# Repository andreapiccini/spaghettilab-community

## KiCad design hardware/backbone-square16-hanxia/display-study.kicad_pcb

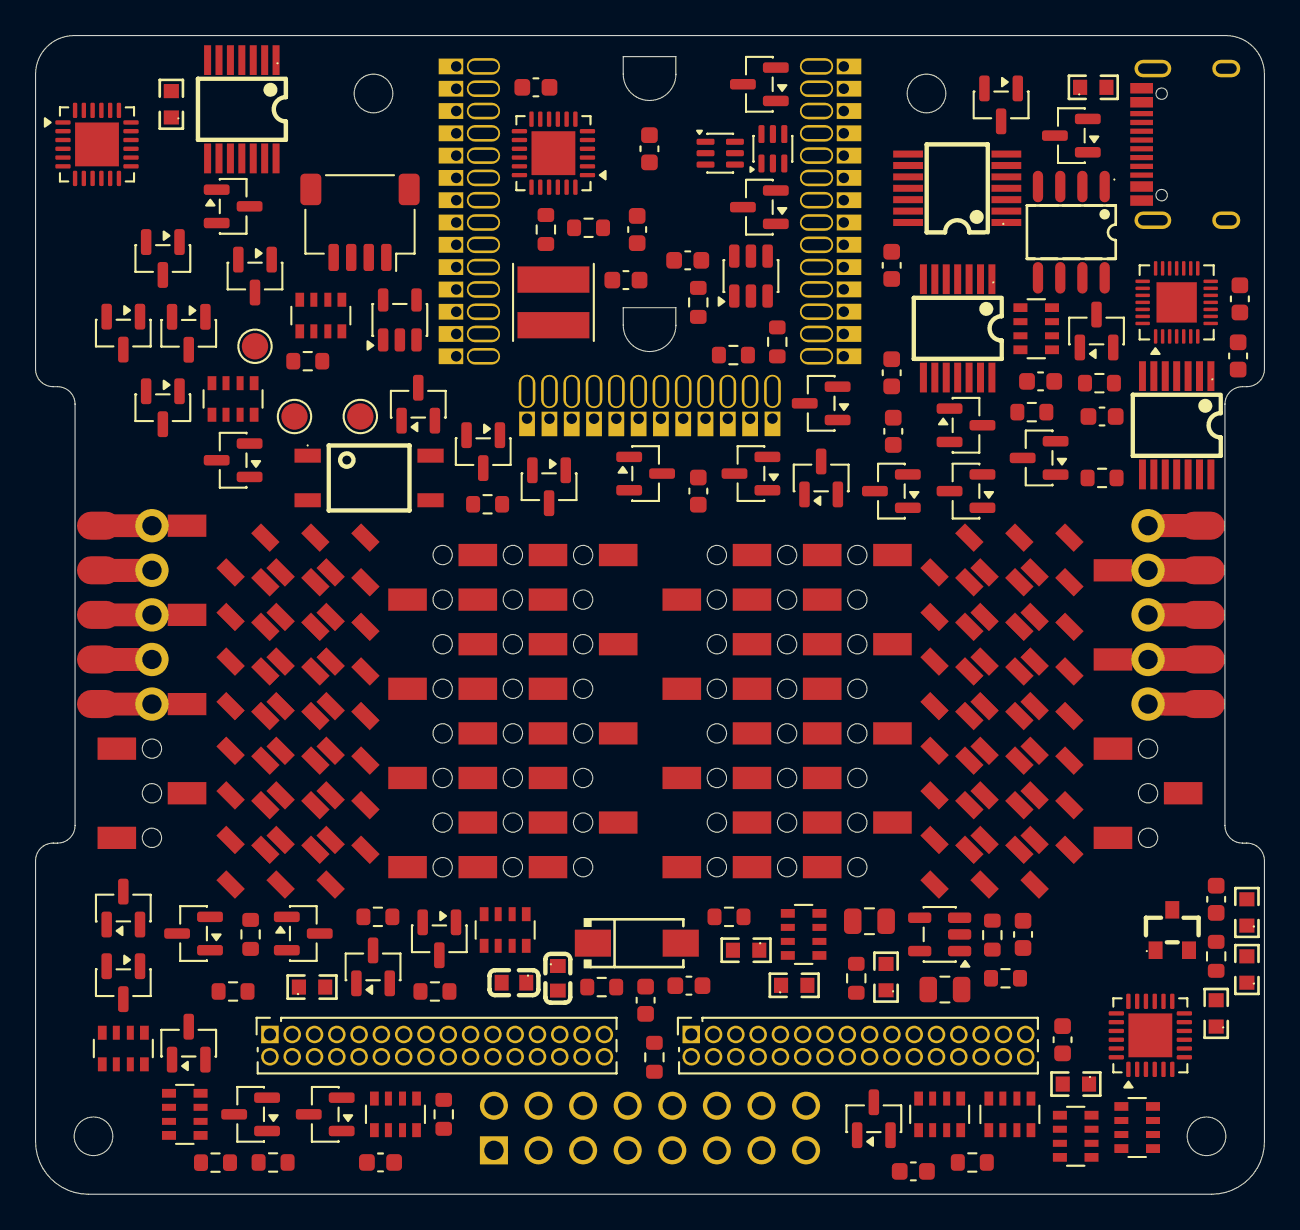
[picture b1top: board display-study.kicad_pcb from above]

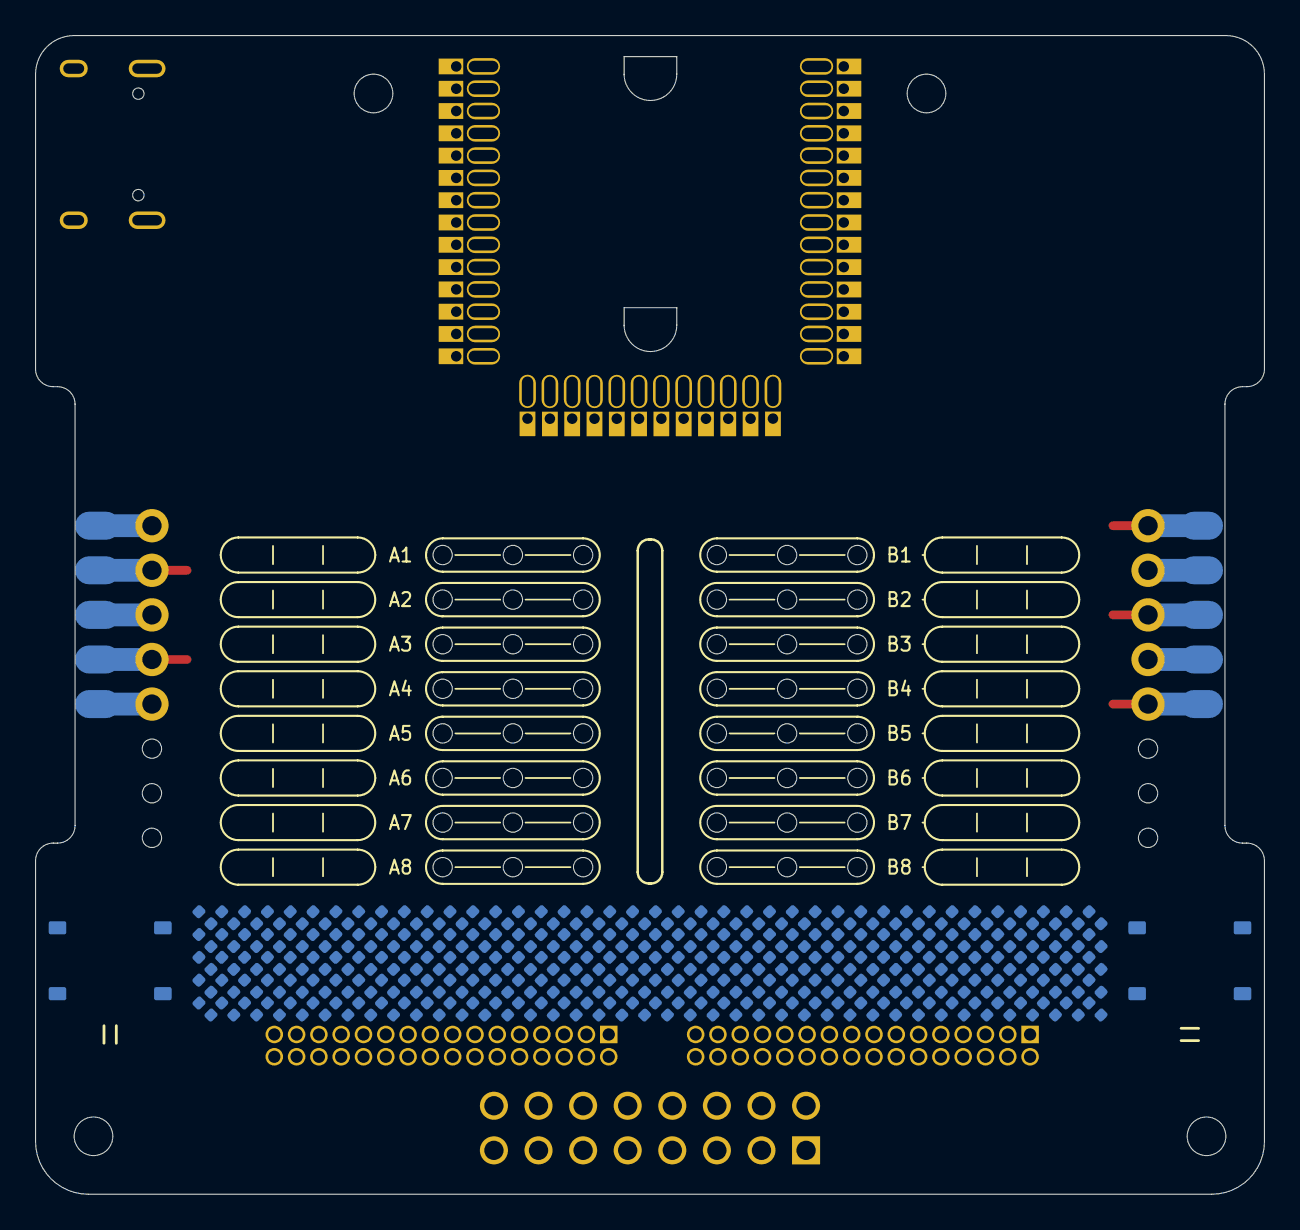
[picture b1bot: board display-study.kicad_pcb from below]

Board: 4 copper layers, 70.0 x 66.0 mm, 395 parts (203 on the bottom side), 150 nets.

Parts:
C1: 100nF/50V; C0603
C5, C9, C86: 22uF; C_0603_1608Metric
C11: 1uF; C0603
C74, C200, C204, C205, C206, C238, C239, C241, C242, C400, C402: 100nF; C_0603_1608Metric
C84: 22pF; C_0603_1608Metric
C85: 100nF/50V; C_0603_1608Metric
C139, C140: 10nF; C_0603_1608Metric
C299: 1nF; C_0603_1608Metric
C300, C301: 10uF 25V; C_0805_2012Metric
C401: 1uF; C_0603_1608Metric
D6: SS54_C22452; SMA_L4.4-W2.8-LS5.4-R-RD
D7: BAV70; SOT-23
D400, D403, D406, D409, D412, D415, D418, D421, D424, D427, D430, D433, D436, D439, D442, D445: XL-3216SURC-FB; XINGLIGHT_XL3216_Reverse_Word_Window
D401, D404, D407, D410, D413, D416, D419, D422, D425, D428, D431, D434, D437, D440, D443, D446: XL-3216UBC-FB; XINGLIGHT_XL3216_Reverse_Word_Window
D402, D405, D408, D411, D414, D417, D420, D423, D426, D429, D432, D435, D438, D441, D444, D447: XL-3216UGC-FB; XINGLIGHT_XL3216_Reverse_Word_Window
D500, D501, D502, D503, D504, D505, D506, D507, D508, D509, D510, D511, D512, D513, D514, D515, D516, D517, D518, D519, D520, D521, D522, D523, D524, D525, D526, D527, D528, D529, D530, D531, D532, D533, D534, D535, D536, D537, D538, D539, D540, D541, D542, D543, D544, D545, D546, D547, D548, D549, D550, D551, D552, D553, D554, D555, D556, D557, D558, D559, D560, D561, D562, D563, D564, D565, D566, D567, D568, D569, D570, D571, D572, D573, D574, D575, D576, D577, D578, D579, D580, D581, D582, D583, D584, D585, D586, D587, D588, D589, D590, D591, D592, D593, D594, D595, D596, D597, D598, D599, D600, D601, D602, D603, D604, D605, D606, D607, D608, D609, D610, D611, D612, D613, D614, D615, D616, D617, D618, D619, D620, D621, D622, D623, D624, D625, D626, D627, D628, D629, D630, D631, D632, D633, D634, D635, D636, D637, D638, D639, D640, D641, D642, D643, D644, D645, D646, D647, D648, D649, D650, D651, D652, D653, D654, D655, D656, D657, D658, D659, D660, D661, D662, D663, D664, D665, D666, D667, D668, D669, D670, D671, D672, D673, D674, D675, D676, D677, D678, D679, D680, D681, D682, D683, D684, D685, D686, D687, D688, D689, D690, D691, D692, D693, D694, D695, D696, D697, D698, D699: XL-1005SURC STUDY ONLY; LED_0402_1005Metric
H1, H2, H3, H4: MountingHole; MountingHole_2.2mm_M2_DIN965
J2: FROM_PREVIOUS; Magnetic_J2_PTH_Module
J4: SM04B-SRSS-TB(LF)(SN); JST_SH_SM04B-SRSS-TB_1x04-1MP_P1.00mm_Horizontal
J9: TO NEXT; Magnetic_J9_PTH_Module
J18, J19, J21, J22, J23, J24: HX PM2.54-1x8P TP-YQ; Hanxia_C42380985_1x08_BottomAccess_ContouredCourtyard
J25: BOOMELE 2x8 RA C52105; BOOMELE_C52105_2x08_RightAngle
J26, J27: MEZZ_2x16_P1.27; PinSocket_2x16_P1.27mm_Vertical
J28, J29: HX PM2.54-1x8P TP-YQ; Hanxia_C42380985_1x08_MagneticSharedHoles
L1: 3.3uH; L_XRTC404012S
Q2: AO3401A; SOT-23_L2.9-W1.3-P1.90-LS2.4-BR
Q9: LMBT3946DW1T1G; SOT-363_SC-70-6
Q10: LMBT3904DW1T1G; SOT-363_SC-70-6
Q30, Q31, Q32, Q33, Q34, Q35, Q36, Q37, Q44, Q45, Q46, Q47, Q48, Q49, Q50, Q51: AO3401A; SOT-23
Q100, Q101, Q102, Q103, Q104, Q105, Q106, Q107, Q108, Q109, Q110, Q111, Q112, Q113, Q114, Q115: AO3400A; SOT-23
R4, R123, R125, R126, R130, R203: 10k; R_0603_1608Metric
R5: 470R; R0603
R8: 120R; R0603
R15, R16: 10k; R0603
R17, R18: 33R; R0603
R22, R27: 5.1k; R0603
R24, R25: 4.7k; R0603
R36: 150k; R_0603_1608Metric
R37: 33.2k; R_0603_1608Metric
R104, R400: 47k; R_0603_1608Metric
R110: 56k; R_0603_1608Metric
R111, R124, R127, R129, R132, R200, R201, R202, R301: 100k; R_0603_1608Metric
R128, R131: 22k; R_0603_1608Metric
R300: 6.8k 1%; R_0603_1608Metric
R302, R303: 4.7k; R_0603_1608Metric
RN1, RN2, RN3, RN4, RN5, RN6, RN7, RN8, RN9, RN10, RN11, RN12: 100k; YC164_4x0603_100k
SW1, SW2: TS-1187A-B-A-B; XKB_TS1187A_5.1x5.1_H1.5
TP1: ESP_BOOT; TestPoint_Pad_D1.5mm
TP2: ESP_EN; TestPoint_Pad_D1.5mm
TP3: GND; TestPoint_Pad_D1.5mm
U1: ESP32-S3-WROOM-1-N8R2; ESP32-S3-WROOM-1_FlexyPin_N8R2_TwoSideCourtyard
U2: SN65HVD230DR; SOIC-8_L4.9-W3.9-P1.27-LS6.0-BL
U3: HC-TYPE-C-16P-01A; USB-C-SMD_HC-TYPE-C-16P-01A_ClearSilk
U4: SY8089AAAC; SOT-23-5
U8: G3VM-61VY3; SMD-4_L4.6-W3.7-P2.54-LS7.0-TL
U40, U41, U42: FCA9539Q; FCA9539Q_WQFN24_4x4
U50, U51, U53, U54: 74CBTLV3125PW,118; TSSOP-14_L5.0-W4.4-P0.65-LS6.4-BL
U60: SN74LVC1G97DBVR; SOT-23-6
U63: SY6280AAAC; SOT-23-5
U70: IS31FL3731-QFLS2-TR; IS31FL3731_QFN28_4x4

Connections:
3V3: C1.1, C9.1, C74.2, C84.1, C86.1, C200.1, C204.1, C205.1, C206.1, C238.1, C239.1, C241.1, C242.1, C300.1, J4.2 (+3V3), J25.3, J26.30, J27.28, J28.6, J29.6, L1.2, R15.1, R16.1, R24.1, R25.1, R36.1, R104.1, R302.1, R303.1, RN9.1, RN9.2, RN9.3, RN9.4, RN10.1, RN10.2, RN10.3, RN10.4, RN11.1, RN11.2, RN11.3, RN11.4, RN12.1, RN12.2, RN12.3, RN12.4, U1.2 (3V3), U2.3, U40.18, U40.21, U41.21, U41.23, U42.18, U42.21, U42.23, U50.14, U51.14, U53.14, U54.14, U60.5, U63.5
3V3_ROWS: C301.1, Q30.2, Q31.2, Q32.2, Q33.2, Q34.2, Q35.2, Q36.2, Q37.2, Q44.2, Q45.2, Q46.2, Q47.2, Q48.2, Q49.2, Q50.2, Q51.2, RN1.1, RN1.2, RN1.3, RN1.4, RN2.1, RN2.2, RN2.3, RN2.4, RN3.1, RN3.2, RN3.3, RN3.4, RN4.1, RN4.2, RN4.3, RN4.4, U63.1
5V: C5.1, C85.1, C140.1, C400.1, C401.1, D6.2, J2.1, J9.1, J25.4, J27.30, J28.5, J29.5, Q2.2, Q9.4, R4.1, R125.1, R127.1, R130.1, U4.1, U4.4, U70.2
BUCK_FB: C84.2, R36.2, R37.1, U4.5
BUCK_SW: L1.1, U4.3
CAN_H: J2.2, J9.2, J28.4, J29.4, R8.1, U2.7
CAN_L: J2.3, J9.3, J28.3, J29.3, U2.6, U8.4
CAN_RX: U1.11 (IO18), U2.4
CAN_TX: R104.2, U1.10 (IO17), U2.1
ESP_BOOT: R15.2, TP1.1, U1.27 (IO0), U60.6
ESP_EN: C11.2, J26.32, R16.2, TP2.1, U1.3 (EN), U60.1, U70.3
EXP_RESET_N: J27.32, R203.1, R301.1, U40.24, U41.24, U42.24, U60.4, U63.4
GND: C1.2, C5.2, C9.2, C11.1, C74.1, C85.2, C86.2, C139.2, C200.2, C204.2, C205.2, C206.2, C238.2, C239.2, C241.2, C242.2, C299.2, C300.2, C301.2, C400.2, C401.2, C402.2, J2.5, J4.1 (GND), J9.5, J25.1, J25.2, J25.14, J26.17, J26.19, J26.21, J26.23, J26.25, J26.27, J26.29, J26.31, J27.17, J27.19, J27.21, J27.23, J27.25, J27.27, J27.29, J27.31, J28.1, J29.1, Q9.1, Q10.1, Q10.4, Q100.2, Q101.2, Q102.2, Q103.2, Q104.2, Q105.2, Q106.2, Q107.2, Q108.2, Q109.2, Q110.2, Q111.2, Q112.2, Q113.2, Q114.2, Q115.2, R22.2, R27.1, R37.2, R111.2, R124.2, R129.2, R132.2, R200.2, R201.2, R202.2, R203.2, R300.2, R301.2, R400.2, RN5.5, RN5.6, RN5.7, RN5.8, RN6.5, RN6.6, RN6.7, RN6.8, RN7.5, RN7.6, RN7.7, RN7.8, RN8.5, RN8.6, RN8.7, RN8.8, SW1.2, SW2.2, TP3.1, U1.1 (GND), U1.40 (GND), U2.2, U2.8, U3.1 (SHELL), U3.2 (SHELL), U3.3 (SHELL), U3.4 (SHELL), U3.A1B12 (GND), U3.B1A12 (GND), U4.2, U8.2, U40.9, U40.23, U40.25, U41.9, U41.18, U41.25, U42.9, U42.25, U50.7, U51.7, U53.7, U54.7, U60.2, U60.3, U63.2, U70.5, U70.17, U70.18, U70.29
GPIO1: J26.2, U1.39 (IO1), U50.2
GPIO2: J26.4, U1.38 (IO2), U50.5
GPIO3: J26.6, R200.1, U1.15 (IO3), U50.9
GPIO6: J26.8, U1.6 (IO6), U50.12
GPIO7: J26.10, U1.7 (IO7), U51.2
GPIO8: J26.12, U1.12 (IO8), U51.5
GPIO9: J26.14, U1.17 (IO9), U51.9
GPIO10: J26.16, U1.18 (IO10), U51.12
GPIO13: J25.7, J26.22, SW2.1, U1.21 (IO13)
GPIO15: J25.8, J26.24, U1.8 (IO15)
GPIO16: J25.9, J26.26, U1.9 (IO16)
GPIO35: J27.2, U1.28 (IO35), U53.2
GPIO36: J27.4, U1.29 (IO36), U53.5
GPIO37: J27.6, U1.30 (IO37), U53.9
GPIO38: J27.8, U1.31 (IO38), U53.12
GPIO39: J27.10, U1.32 (IO39), U54.2
GPIO40: J27.12, U1.33 (IO40), U54.5
GPIO41: J27.14, U1.34 (IO41), U54.9
GPIO42: J27.16, U1.35 (IO42), U54.12
GPIO43: J25.10, J27.18, U1.37 (TXD0)
GPIO44: J25.11, J27.20, U1.36 (RXD0)
GPIO45: R201.1, U1.26 (IO45)
GPIO46: R202.1, U1.16 (IO46)
GPIO47: J25.12, J27.22, U1.24 (IO47)
GPIO48: J25.13, J27.24, U1.25 (IO48)
I2C_INT_SCL: R303.2, U1.5 (IO5), U40.19, U41.19, U42.19, U70.20
I2C_INT_SDA: R302.2, U1.4 (IO4), U40.20, U41.20, U42.20, U70.19
I2C_USER_SCL: J4.4 (SCL), J25.6, J25.16, J26.20, J27.26, J28.8, J29.8, R25.2, U1.20 (IO12)
I2C_USER_SDA: J4.3 (SDA), J25.5, J25.15, J26.18, J26.28, J28.7, J29.7, R24.2, U1.19 (IO11)
LABEL_CA1: D400.1, D403.1, D406.1, D409.1, D412.1, D415.1, D418.1, D421.1, D424.2, U70.21
LABEL_CA2: D400.2, D424.1, D427.1, D430.1, D433.1, D436.1, D439.1, D442.1, D445.1, U70.22
LABEL_CA3: D403.2, D427.2, U70.23
LABEL_CA4: D406.2, D430.2, U70.24
LABEL_CA5: D409.2, D433.2, U70.25
LABEL_CA6: D412.2, D436.2, U70.26
LABEL_CA7: D415.2, D439.2, U70.27
LABEL_CA8: D418.2, D442.2, U70.28
LABEL_CA9: D421.2, D445.2, U70.1
LABEL_CB1: D401.1, D402.1, D404.1, D405.1, D407.1, D408.1, D410.1, D411.1, D413.2, D425.2, D437.2, U70.7
LABEL_CB2: D401.2, D413.1, D414.1, D416.1, D417.1, D419.1, D420.1, D422.1, D423.1, D426.2, D438.2, U70.8
LABEL_CB3: D402.2, D414.2, D425.1, D426.1, D428.1, D429.1, D431.1, D432.1, D434.1, D435.1, D440.2, U70.9
LABEL_CB4: D404.2, D416.2, D428.2, D437.1, D438.1, D440.1, D441.1, D443.1, D444.1, D446.1, D447.1, U70.10
LABEL_CB5: D405.2, D417.2, D429.2, D441.2, U70.11
LABEL_CB6: D407.2, D419.2, D431.2, D443.2, U70.12
LABEL_CB7: D408.2, D420.2, D432.2, D444.2, U70.13
LABEL_CB8: D410.2, D422.2, D434.2, D446.2, U70.14
LABEL_CB9: D411.2, D423.2, D435.2, D447.2, U70.15
LABEL_C_FILT: C402.1, U70.16
LABEL_R_EXT: R400.1, U70.6
unnamed: R300.1, U63.3
ROW_L01: J18.1, J19.1, J21.1, J26.1, Q30.3, Q100.3, U50.3
ROW_L01_ISO_N: RN9.5, U42.1, U50.1
ROW_L01_NG: Q100.1, RN5.1, U40.2
ROW_L01_PG: Q30.1, RN1.5, U40.1
ROW_L02: J18.2, J19.2, J21.2, J26.3, Q31.3, Q101.3, U50.6
ROW_L02_ISO_N: RN9.6, U42.2, U50.4
ROW_L02_NG: Q101.1, RN5.2, U40.4
ROW_L02_PG: Q31.1, RN1.6, U40.3
ROW_L03: J18.3, J19.3, J21.3, J26.5, Q32.3, Q102.3, U50.8
ROW_L03_ISO_N: RN9.7, U42.3, U50.10
ROW_L03_NG: Q102.1, RN5.3, U40.6
ROW_L03_PG: Q32.1, RN1.7, U40.5
ROW_L04: J18.4, J19.4, J21.4, J26.7, Q33.3, Q103.3, U50.11
ROW_L04_ISO_N: RN9.8, U42.4, U50.13
ROW_L04_NG: Q103.1, RN5.4, U40.8
ROW_L04_PG: Q33.1, RN1.8, U40.7
ROW_L05: J18.5, J19.5, J21.5, J26.9, Q34.3, Q104.3, U51.3
ROW_L05_ISO_N: RN10.5, U42.5, U51.1
ROW_L05_NG: Q104.1, RN6.1, U40.11
ROW_L05_PG: Q34.1, RN2.5, U40.10
ROW_L06: J18.6, J19.6, J21.6, J26.11, Q35.3, Q105.3, U51.6
ROW_L06_ISO_N: RN10.6, U42.6, U51.4
ROW_L06_NG: Q105.1, RN6.2, U40.13
ROW_L06_PG: Q35.1, RN2.6, U40.12
ROW_L07: J18.7, J19.7, J21.7, J26.13, Q36.3, Q106.3, U51.8
ROW_L07_ISO_N: RN10.7, U42.7, U51.10
ROW_L07_NG: Q106.1, RN6.3, U40.15
ROW_L07_PG: Q36.1, RN2.7, U40.14
ROW_L08: J18.8, J19.8, J21.8, J26.15, Q37.3, Q107.3, U51.11
ROW_L08_ISO_N: RN10.8, U42.8, U51.13
ROW_L08_NG: Q107.1, RN6.4, U40.17
ROW_L08_PG: Q37.1, RN2.8, U40.16
ROW_R01: J22.1, J23.1, J24.1, J27.1, Q44.3, Q108.3, U53.3
ROW_R01_ISO_N: RN11.5, U42.10, U53.1
ROW_R01_NG: Q108.1, RN7.1, U41.2
ROW_R01_PG: Q44.1, RN3.5, U41.1
ROW_R02: J22.2, J23.2, J24.2, J27.3, Q45.3, Q109.3, U53.6
ROW_R02_ISO_N: RN11.6, U42.11, U53.4
ROW_R02_NG: Q109.1, RN7.2, U41.4
ROW_R02_PG: Q45.1, RN3.6, U41.3
ROW_R03: J22.3, J23.3, J24.3, J27.5, Q46.3, Q110.3, U53.8
ROW_R03_ISO_N: RN11.7, U42.12, U53.10
ROW_R03_NG: Q110.1, RN7.3, U41.6
ROW_R03_PG: Q46.1, RN3.7, U41.5
ROW_R04: J22.4, J23.4, J24.4, J27.7, Q47.3, Q111.3, U53.11
ROW_R04_ISO_N: RN11.8, U42.13, U53.13
ROW_R04_NG: Q111.1, RN7.4, U41.8
ROW_R04_PG: Q47.1, RN3.8, U41.7
ROW_R05: J22.5, J23.5, J24.5, J27.9, Q48.3, Q112.3, U54.3
ROW_R05_ISO_N: RN12.5, U42.14, U54.1
ROW_R05_NG: Q112.1, RN8.1, U41.11
ROW_R05_PG: Q48.1, RN4.5, U41.10
ROW_R06: J22.6, J23.6, J24.6, J27.11, Q49.3, Q113.3, U54.6
ROW_R06_ISO_N: RN12.6, U42.15, U54.4
ROW_R06_NG: Q113.1, RN8.2, U41.13
ROW_R06_PG: Q49.1, RN4.6, U41.12
ROW_R07: J22.7, J23.7, J24.7, J27.13, Q50.3, Q114.3, U54.8
ROW_R07_ISO_N: RN12.7, U42.16, U54.10
ROW_R07_NG: Q114.1, RN8.3, U41.15
ROW_R07_PG: Q50.1, RN4.7, U41.14
ROW_R08: J22.8, J23.8, J24.8, J27.15, Q51.3, Q115.3, U54.11
ROW_R08_ISO_N: RN12.8, U42.17, U54.13
ROW_R08_NG: Q115.1, RN8.4, U41.17
ROW_R08_PG: Q51.1, RN4.8, U41.16
TERM_ABSENT_L: D7.1, Q9.6, R125.2
TERM_ABSENT_OR: D7.3, R131.1
TERM_ABSENT_R: D7.2, Q10.6, R130.2
TERM_BASE_DRIVE: Q10.5, R131.2, R132.1
TERM_BASE_INV: Q10.2, R128.2, R129.1
TERM_BASE_L: C139.1, Q9.2, R123.2, R124.1
TERM_BASE_R: C140.2, Q9.5, R126.2, R127.2
TERM_CTRL_IN: J2.4, J29.2, R123.1
TERM_CTRL_OUT: J9.4, J28.2, R126.1
TERM_DRIVE: Q2.3, R5.2
TERM_GATE_N: Q2.1, Q10.3, R4.2
TERM_LED: R5.1, U8.1
TERM_PRESENT_R: Q9.3, R128.1
TERM_R: R8.2, U8.3
UI_BANK_N: SW1.1, U1.23 (IO21)
USB_CC1: R22.1, U3.A5 (CC1)
USB_CC2: R27.2, U3.B5 (CC2)
USB_D+: R17.1, U3.A6 (D+), U3.B6 (D+)
USB_D-: R18.1, U3.A7 (D-), U3.B7 (D-)
USB_ESP_D+: R17.2, U1.14 (USB_D+)
USB_ESP_D-: R18.2, U1.13 (USB_D-)
USB_VBUS_PRESENT: C299.1, R110.2, R111.1, U1.22 (IO14)
VBUS: D6.1, R110.1, U3.A4B9 (VBUS), U3.B4A9 (VBUS)

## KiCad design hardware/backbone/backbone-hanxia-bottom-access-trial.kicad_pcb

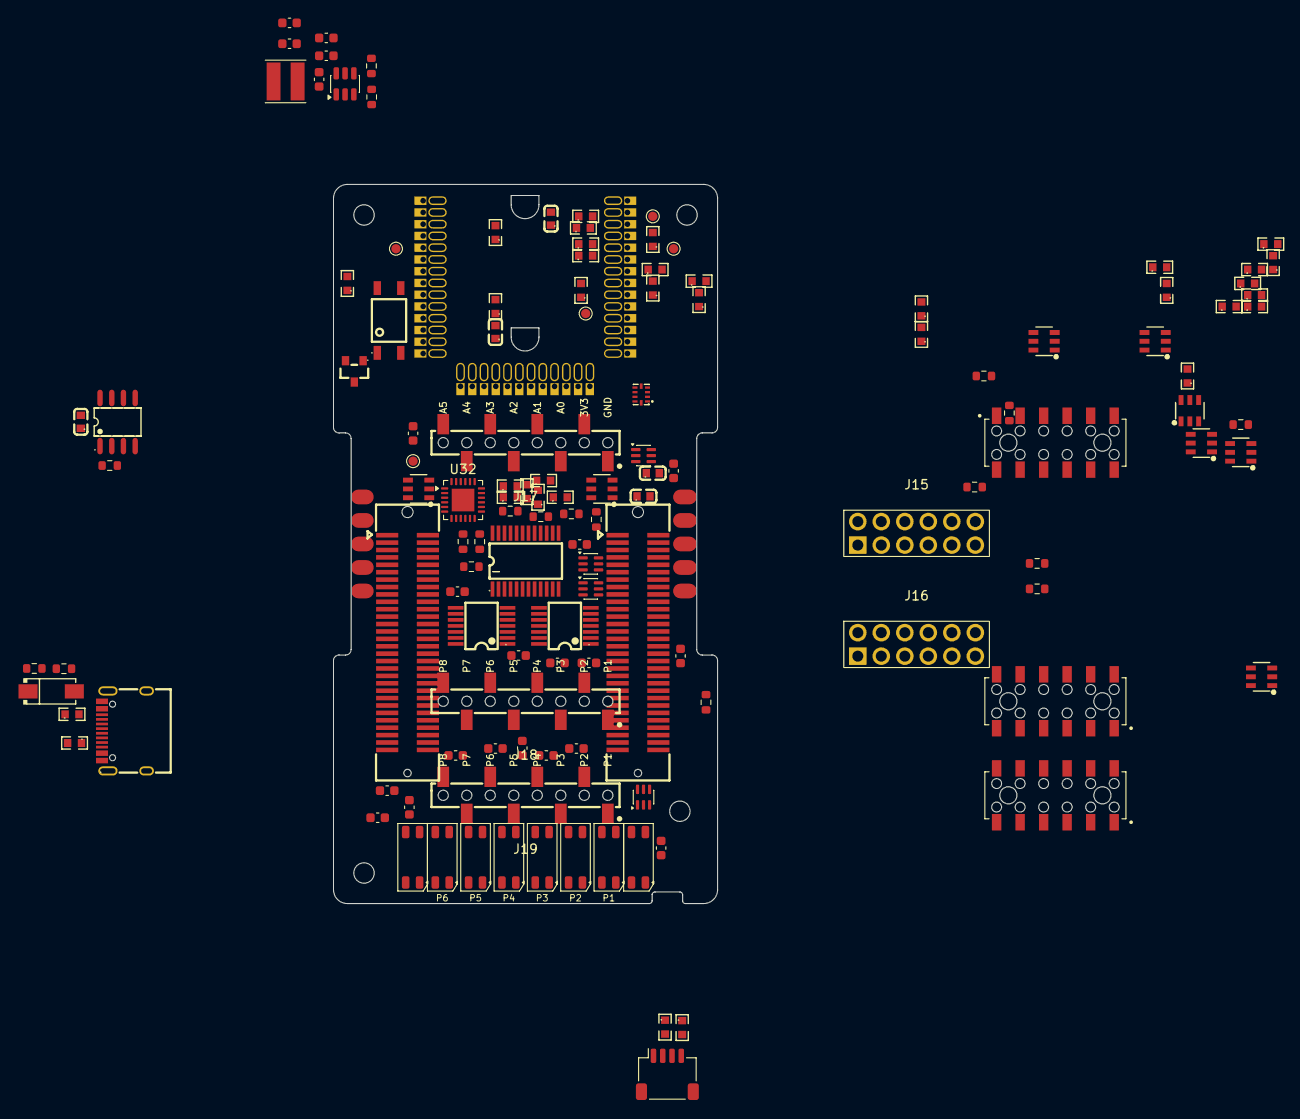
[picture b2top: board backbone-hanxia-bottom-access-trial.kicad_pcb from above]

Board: 4 copper layers, 41.5 x 77.7 mm, 136 parts (1 on the bottom side), 117 nets, no tracks yet.

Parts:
C1, C74, C88, C89: 100nF; C0603
C5, C9, C86: 22uF; C_0603_1608Metric
C11: 1uF; C0603
C84, C85: 100nF/50V; C_0603_1608Metric
C119, C124, C125, C126, C127, C128, C129, C130, C132, C133, C134, C135, C136, C137, C138, C139, C140: 100nF; C_0603_1608Metric
D6: SS54_C22452; SMA_L4.4-W2.8-LS5.4-R-RD
H1, H2, H3, H4: MountingHole; MountingHole_2.2mm_M2_DIN965
J1, J3, J140: M20-7810645R; HARWIN_M20-7810645R
J2: FROM_PREVIOUS; Magnetic_J2_Edge_DualFace
J4: SM04B-SRSS-TB(LF)(SN); JST_SH_SM04B-SRSS-TB_1x04-1MP_P1.00mm_Horizontal
J9: TO NEXT; Magnetic_J9_Edge_DualFace
J10, J11: 61082-061402LF; CONN-SMD_61082-061402LF
J15, J16: A2541HWV-2x6P; CJT_A2541HWV-2x6P_P2.54mm_Vertical
J17, J18, J19: HX PM2.54-1x8P TP-YQ; Hanxia_C42380985_1x08_BottomAccess_Trial
L1: 3.3uH; L_XRTC404012S
LED1, LED2, LED3, LED4, LED5, LED6, LED7, LED8: SK6812MINI-E; LED_SK6812MINI-E_FR4_Window_HandFormed
Q2: AO3401A; SOT-23_L2.9-W1.3-P1.90-LS2.4-BR
Q3, Q4, Q5, Q6, Q7, Q8, Q9, Q10: AO6604; SOT-23-6_L2.9-W1.6-P0.95-LS2.8-BL
R4: 470k; R0603
R5: 1k; R0603
R8: 120R; R0603
R15, R16: 10k; R0603
R17, R18: 33R / ESP USB; R0603
R22, R27: 5.1k; R0603
R24, R25: 4.7k; R0603
R36: 33k 1%; R_0603_1608Metric
R37: 10k 1%; R_0603_1608Metric
R38, R39, R40, R41, R42, R43, R44, R45, R46, R47, R48, R49, R50, R51, R52, R53, R54, R55, R116, R117, R119, R120, R122, R123: 100k; R0603
R56, R57, R58, R59, R60, R61, R118, R121: 0.1R; R_0603_1608Metric
R103, R105, R110, R111, R115: 100k; R_0603_1608Metric
R104: 47k; R_0603_1608Metric
R112, R113, R114: 0R DNP / PSRAM GUARD; R_0603_1608Metric
TP8, TP9, TP12, TP13, TP15: SMD/0.6mm; TestPoint_Pad_D1.0mm
U1: ESP32-S3-WROOM-1_1U_FlexyPin_Socket
U2: SN65HVD230DR; SOIC-8_L4.9-W3.9-P1.27-LS6.0-BL
U3: HC-TYPE-C-16P-01A; USB-C-SMD_HC-TYPE-C-16P-01A
U4: TPS562201DDCR; TSOT-23-6_Power
U8: G3VM-61VY3; SMD-4_L4.6-W3.7-P2.54-LS7.0-TL
U12, U13: SN74CBTLV3125PWR; TSSOP-14_L5.0-W4.4-P0.65-LS6.4-BL
U25: TCA9535PWR(UMW); TSSOP-24_L7.8-W4.4-P0.65-LS6.4-BL
U26, U27, U28, U29: SN74LVC1G3157DCKR; SOT-363_SC-70-6
U31: TS3USB221ARSER; UQFN-10_L2.0-W1.5-P0.50-BL
U32: TCA9535RGER; VQFN-24-1EP_4x4mm_P0.5mm_EP2.45x2.45mm

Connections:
5V: C5.1, C85.1, D6.2 (K), J2.1, J2.4, J9.1, J10.1, J10.2, J11.1, J11.2, Q2.2 (S), U4.3 (VIN), U4.5 (EN)
/BUCK_BOOT: C84.1, U4.6 (VBST)
/BUCK_FB: R36.2, R37.1, U4.4 (VFB)
/BUCK_SW: C84.2, L1.1, U4.2 (SW)
/LED_CHAIN_1: LED1.4 (DOUT), LED2.2 (DIN)
/LED_CHAIN_2: LED2.4 (DOUT), LED3.2 (DIN)
/LED_CHAIN_3: LED3.4 (DOUT), LED4.2 (DIN)
/LED_CHAIN_4: LED4.4 (DOUT), LED5.2 (DIN)
/LED_CHAIN_5: LED5.4 (DOUT), LED6.2 (DIN)
/LED_CHAIN_6: LED6.4 (DOUT), LED7.2 (DIN)
/LED_CHAIN_7: LED7.4 (DOUT), LED8.2 (DIN)
/TERM_DRIVE: Q2.3 (D), R5.2
/TERM_LED: R5.1, U8.1
/TERM_R: R8.2, U8.3
/USB_CC1: R22.1, U3.A5 (CC1)
/USB_CC2: R27.2, U3.B5 (CC2)
A0: J3.7, J10.6, J17.3, U1.7 (IO7), U12.2 (A)
A1: J3.1, J10.9, J17.4, U1.12 (IO8), U12.5 (A)
A2: J3.12, J10.13, J17.5, U1.17 (IO9), U12.9 (A)
A3: J3.10, J10.17, J17.6, U1.18 (IO10), U12.12 (A)
A4: J3.8, J10.21, J17.7, U1.39 (IO1), U13.2 (A)
A5: J3.6, J10.24, J17.8, U1.38 (IO2), U13.5 (A)
AG_CAN_TX: J10.34, U26.1
AG_ISO4_N: J10.36, U28.1
AG_ISO5_N: J10.37, U29.1
AG_LED_DATA: J10.38, U27.1
ALED: LED1.2 (DIN), R105.1, U27.4
BOOT: J10.28, R15.2, TP9.1 (1_1), U1.27 (IO0)
CAN_H: J2.2, J9.2, J11.46, R8.1, U2.7 (CANH)
CAN_L: J2.3, J9.3, J11.47, U2.6 (CANL), U8.4
CAN_RX: J10.39, U1.11 (IO18), U2.4 (R)
CAN_TX: R104.2, U2.1 (D), U26.4
CTRL13: J10.41, U1.21 (IO13)
CTRL14: J10.42, U1.22 (IO14)
ESP35_AUX: J10.43, R112.2
ESP36_AUX: J10.44, R113.2
ESP37_AUX: J10.46, R114.2
ESP_AG_BOOT0: J10.29, U1.8 (IO15)
ESP_AG_RESET_N: J10.31, U1.9 (IO16)
ESP_CAN_TX: J10.47, U1.10 (IO17), U26.3
ESP_ISO4_N: J10.48, U1.32 (IO39), U28.3
ESP_ISO5_N: J10.49, U1.33 (IO40), U29.3
ESP_LED_DATA: J10.51, U1.23 (IO21), U27.3
ESP_PROG_RX: J10.32, U1.25 (IO48)
ESP_PROG_TX: J10.33, U1.24 (IO47)
EXT_SPI_CS_N: J10.52, U1.19 (IO11), U13.12 (A)
GND: C1.2, C5.2, C9.2, C11.1, C74.1, C85.2, C86.2, C88.2, C89.2, C119.2, C124.2, C125.2, C126.2, C127.2, C128.2, C129.2, C130.2, C132.2, C133.2, C134.2, C135.2, C136.2, C137.2, C138.2, C139.2, C140.2, J2.5, J3.4, J3.5, J3.9, J4.1 (GND), J9.5, J10.5, J10.10, J10.15, J10.20, J10.25, J10.30, J10.35, J10.40, J10.45, J10.50, J10.57, J10.58, J10.59, J10.60, J11.5, J11.10, J11.15, J11.20, J11.25, J11.30, J11.35, J11.40, J11.45, J11.50, J11.55, J11.57, J11.58, J11.59, J11.60, J17.1, LED1.1 (GND), LED2.1 (GND), LED3.1 (GND), LED4.1 (GND), LED5.1 (GND), LED6.1 (GND), LED7.1 (GND), LED8.1 (GND), Q3.5 (S), Q4.5 (S), Q5.5 (S), Q6.5 (S), Q7.5 (S), Q8.5 (S), Q9.5, Q10.5, R4.1, R22.2, R27.1, R37.2, R39.2, R41.2, R43.2, R45.2, R47.2, R49.2, R103.2, R105.2, R111.2, R117.2, R120.2, TP12.1 (1_1), TP13.1 (1_1), U1.1 (GND), U1.40 (GND), U2.2 (GND), U2.8 (RS), U3.1 (SHELL), U3.2 (SHELL), U3.3 (SHELL), U3.4 (SHELL), U3.A1B12 (GND), U3.B1A12 (GND), U4.1 (GND), U8.2, U12.7 (GND), U13.7 (GND), U25.2, U25.3, U25.12, U25.21, U26.2, U27.2, U28.2, U29.2, U31.5, U31.6, U32.9, U32.23, U32.24, U32.25
IO3: J10.53, U1.15 (IO3), U13.9 (A)
IO4: J4.3 (SDA), J10.54, R24.2, U1.4 (IO4), U25.23, U32.20
IO5: J4.4 (SCL), J11.7, R25.2, U1.5 (IO5), U25.22, U32.19
IO35: R112.1, U1.28 (IO35)
IO36: R113.1, U1.29 (IO36)
IO37: R114.1, U1.30 (IO37)
IO45: J10.56, U1.26 (IO45)
IO46: J11.6, U1.16 (IO46)
ISO_A0_N: J11.41, R50.2, U12.1 (~OE), U25.17
ISO_A1_N: J11.42, R51.2, U12.4 (~OE), U25.18
ISO_A2_N: J11.43, R52.2, U12.10 (~OE), U25.19
ISO_A3_N: J11.44, R53.2, U12.13 (~OE), U25.20
ISO_A4_N: J11.8, R54.2, U13.1 (~OE), U28.4
ISO_A5_N: J11.9, R55.2, U13.4 (~OE), U29.4
ISO_A6_N: R122.2, U13.10 (~OE), U32.3
ISO_A7_N: R123.2, U13.13 (~OE), U32.6
LED_EXP_DATA: J11.52, LED8.4 (DOUT)
MEAS_INHIBIT: J11.11, U1.35 (IO42)
MEAS_S0: J11.12, U1.6 (IO6)
MEAS_S1: J11.13, U1.20 (IO12)
MEAS_S2: J11.14, U1.34 (IO41)
MEZZ_OWNER: J11.16, R103.1, U26.6, U27.6, U28.6, U29.6, U31.9
MEZZ_PRESENT_N: J11.17, R115.2, U1.31 (IO38)
N_A0: J10.7, Q3.4 (D), Q3.6 (D), R56.1, U12.3 (B)
N_A1: J10.11, Q4.4 (D), Q4.6 (D), R57.1, U12.6 (B)
N_A2: J10.14, Q5.4 (D), Q5.6 (D), R58.1, U12.8 (B)
N_A3: J10.18, Q6.4 (D), Q6.6 (D), R59.1, U12.11 (B)
N_A4: J10.22, Q7.4 (D), Q7.6 (D), R60.1, U13.3 (B)
N_A5: J10.26, Q8.4 (D), Q8.6 (D), R61.1, U13.6 (B)
N_A6: J11.53, Q9.4, Q9.6, R118.1, U13.8 (B)
N_A7: J11.56, Q10.4, Q10.6, R121.1, U13.11 (B)
N_GATE_0: J11.27, Q3.1 (G), R39.1, U25.5
N_GATE_1: J11.29, Q4.1 (G), R41.1, U25.7
N_GATE_2: J11.32, Q5.1 (G), R43.1, U25.9
N_GATE_3: J11.34, Q6.1 (G), R45.1, U25.11
N_GATE_4: J11.37, Q7.1 (G), R47.1, U25.14
N_GATE_5: J11.39, Q8.1 (G), R49.1, U25.16
N_GATE_6: Q9.1, R117.1, U32.2
N_GATE_7: Q10.1, R120.1, U32.5
PORT_A0: J1.1, J1.2, J10.8, J18.1, J19.1, J140.1, J140.2, R56.2
PORT_A1: J1.3, J1.4, J10.12, J18.2, J19.2, J140.3, J140.4, R57.2
PORT_A2: J1.5, J1.6, J10.16, J18.3, J19.3, J140.5, J140.6, R58.2
PORT_A3: J1.7, J1.8, J10.19, J18.4, J19.4, J140.7, J140.8, R59.2
PORT_A4: J1.9, J1.10, J10.23, J18.5, J19.5, J140.9, J140.10, R60.2
PORT_A5: J1.11, J1.12, J10.27, J18.6, J19.6, J140.11, J140.12, R61.2
PORT_A6: J11.54, J18.7, J19.7, R118.2
PORT_A7: J10.55, J18.8, J19.8, R121.2
P_GATE_0: J11.26, Q3.3 (G), R38.2, U25.4
P_GATE_1: J11.28, Q4.3 (G), R40.2, U25.6
P_GATE_2: J11.31, Q5.3 (G), R42.2, U25.8
P_GATE_3: J11.33, Q6.3 (G), R44.2, U25.10
P_GATE_4: J11.36, Q7.3 (G), R46.2, U25.13
P_GATE_5: J11.38, Q8.3 (G), R48.2, U25.15
P_GATE_6: Q9.3, R116.2, U32.1
P_GATE_7: Q10.3, R119.2, U32.4
SPI_MISO: J11.18, U1.36 (RXD0)
SPI_MOSI: J11.19, U1.37 (TXD0)
TERM_CTRL_OUT: J9.4, J11.49, Q2.1 (G), R4.2
USB_D+: U3.A6 (D+), U3.B6 (D+), U31.8
USB_D-: U3.A7 (D-), U3.B7 (D-), U31.7
USB_ESP_D+: R17.2, U1.14 (USB_D+)
USB_ESP_D-: R18.2, U1.13 (USB_D-)
USB_SW_AG_N: J11.21, U31.4
USB_SW_AG_P: J11.22, U31.3
USB_SW_ESP_N: R18.1, U31.2
USB_SW_ESP_P: R17.1, U31.1
USB_VBUS_SENSE: J11.23, R110.2, R111.1
VBUS: D6.1 (A), J11.51, R110.1, U3.A4B9 (VBUS), U3.B4A9 (VBUS)
VCORE: C1.1, C9.1, C74.2, C86.1, C88.1, C89.1, C119.1, C124.1, C125.1, C126.1, C127.1, C128.1, C129.1, C130.1, C132.1, C133.1, C134.1, C135.1, C136.1, C137.1, C138.1, C139.1, C140.1, J3.2, J3.3, J3.11, J4.2 (+3V3), J10.3, J10.4, J11.3, J11.4, J17.2, L1.2, LED1.3 (VDD), LED2.3 (VDD), LED3.3 (VDD), LED4.3 (VDD), LED5.3 (VDD), LED6.3 (VDD), LED7.3 (VDD), LED8.3 (VDD), Q3.2 (S), Q4.2 (S), Q5.2 (S), Q6.2 (S), Q7.2 (S), Q8.2 (S), Q9.2, Q10.2, R15.1, R16.1, R24.1, R25.1, R36.1, R38.1, R40.1, R42.1, R44.1, R46.1, R48.1, R50.1, R51.1, R52.1, R53.1, R54.1, R55.1, R104.1, R115.1, R116.1, R119.1, R122.1, R123.1, TP15.1 (1_1), U1.2 (3V3), U2.3 (VCC), U12.14 (VCC), U13.14 (VCC), U25.24, U26.5, U27.5, U28.5, U29.5, U31.10, U32.18, U32.21
~RESET: C11.2, J11.24, R16.2, TP8.1 (1_1), U1.3 (EN)

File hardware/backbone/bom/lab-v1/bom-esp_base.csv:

Reference,Value,Footprint,LCSC,ESP_optional
C1,100nF,SpaghettiLAB:C0603,C1591,no
C5,22uF,Capacitor_SMD:C_0805_2012Metric,C45783,no
C9,22uF,Capacitor_SMD:C_0805_2012Metric,C45783,no
C11,1uF,SpaghettiLAB:C0603,C128624,no
C74,100nF,SpaghettiLAB:C0603,C1591,no
C84,100nF/50V,Capacitor_SMD:C_0603_1608Metric,C14663,no
C85,100nF/50V,Capacitor_SMD:C_0603_1608Metric,C14663,no
C86,22uF,Capacitor_SMD:C_0805_2012Metric,C45783,no
C88,100nF,SpaghettiLAB:C0603,C14663,no
C89,100nF,SpaghettiLAB:C0603,C14663,no
C119,100nF,Capacitor_SMD:C_0603_1608Metric,C14663,no
D6,SS54_C22452,SpaghettiLAB:SMA_L4.4-W2.8-LS5.4-R-RD,C22452,no
H1,MountingHole,MountingHole:MountingHole_2.2mm_M2_DIN965,,no
H2,MountingHole,MountingHole:MountingHole_2.2mm_M2_DIN965,,no
H3,MountingHole,MountingHole:MountingHole_2.2mm_M2_DIN965,,no
H4,MountingHole,MountingHole:MountingHole_2.2mm_M2_DIN965,,no
J1,M20-7810645R,SpaghettiLAB:HARWIN_M20-7810645R,C6585798,no
J2,FROM_PREVIOUS,SpaghettiLAB:Magnetic_J2_Edge_DualFace,C41361292,no
J3,M20-7810645R,SpaghettiLAB:HARWIN_M20-7810645R,C6585798,no
J4,SM04B-SRSS-TB(LF)(SN),SpaghettiLAB:JST_SH_SM04B-SRSS-TB_1x04-1MP_P1.00mm_Horizontal,C160404,no
J5,FH12-24S-0.5SH(55),SpaghettiLAB:Hirose_FH12-24S-0.5SH_1x24-1MP_P0.50mm_Horizontal,C202112,no
J9,TO NEXT,SpaghettiLAB:Magnetic_J9_Edge_DualFace,C41361293,no
J140,M20-7810645R,SpaghettiLAB:HARWIN_M20-7810645R,C6585798,no
L1,3.3uH,SpaghettiLAB:L_XRTC404012S,C39846848,no
LED1,SK6812MINI-E,SpaghettiLAB:LED_SK6812MINI-E_FR4_Window_HandFormed,C5149201,no
LED2,SK6812MINI-E,SpaghettiLAB:LED_SK6812MINI-E_FR4_Window_HandFormed,C5149201,no
LED3,SK6812MINI-E,SpaghettiLAB:LED_SK6812MINI-E_FR4_Window_HandFormed,C5149201,no
LED4,SK6812MINI-E,SpaghettiLAB:LED_SK6812MINI-E_FR4_Window_HandFormed,C5149201,no
LED5,SK6812MINI-E,SpaghettiLAB:LED_SK6812MINI-E_FR4_Window_HandFormed,C5149201,no
LED6,SK6812MINI-E,SpaghettiLAB:LED_SK6812MINI-E_FR4_Window_HandFormed,C5149201,no
NT1,NetTie_2,,,no
Q2,AO3401A,SpaghettiLAB:SOT-23_L2.9-W1.3-P1.90-LS2.4-BR,C15127,no
Q3,AO6604,LCSC_Ports:SOT-23-6_L2.9-W1.6-P0.95-LS2.8-BL,C5182068,no
Q4,AO6604,LCSC_Ports:SOT-23-6_L2.9-W1.6-P0.95-LS2.8-BL,C5182068,no
Q5,AO6604,LCSC_Ports:SOT-23-6_L2.9-W1.6-P0.95-LS2.8-BL,C5182068,no
Q6,AO6604,LCSC_Ports:SOT-23-6_L2.9-W1.6-P0.95-LS2.8-BL,C5182068,no
Q7,AO6604,LCSC_Ports:SOT-23-6_L2.9-W1.6-P0.95-LS2.8-BL,C5182068,no
Q8,AO6604,LCSC_Ports:SOT-23-6_L2.9-W1.6-P0.95-LS2.8-BL,C5182068,no
R4,470k,SpaghettiLAB:R0603,C114622,no
R5,1k,SpaghettiLAB:R0603,C2907002,no
R8,120R,SpaghettiLAB:R0603,C2906988,no
R15,10k,SpaghettiLAB:R0603,C25804,no
R16,10k,SpaghettiLAB:R0603,C25804,no
R17,33R / ESP USB,SpaghettiLAB:R0603,C2909394,no
R18,33R / ESP USB,SpaghettiLAB:R0603,C2909394,no
R22,5.1k,SpaghettiLAB:R0603,C2907044,no
R24,4.7k,SpaghettiLAB:R0603,C23162,no
R25,4.7k,SpaghettiLAB:R0603,C23162,no
R27,5.1k,SpaghettiLAB:R0603,C2907044,no
R36,33k 1%,Resistor_SMD:R_0603_1608Metric,C4216,no
R37,10k 1%,Resistor_SMD:R_0603_1608Metric,C25804,no
R38,100k,SpaghettiLAB:R0603,C25803,no
R39,100k,SpaghettiLAB:R0603,C25803,no
R40,100k,SpaghettiLAB:R0603,C25803,no
R41,100k,SpaghettiLAB:R0603,C25803,no
R42,100k,SpaghettiLAB:R0603,C25803,no
R43,100k,SpaghettiLAB:R0603,C25803,no
R44,100k,SpaghettiLAB:R0603,C25803,no
R45,100k,SpaghettiLAB:R0603,C25803,no
R46,100k,SpaghettiLAB:R0603,C25803,no
R47,100k,SpaghettiLAB:R0603,C25803,no
R48,100k,SpaghettiLAB:R0603,C25803,no
R49,100k,SpaghettiLAB:R0603,C25803,no
R50,100k,SpaghettiLAB:R0603,C25803,no
R51,100k,SpaghettiLAB:R0603,C25803,no
R52,100k,SpaghettiLAB:R0603,C25803,no
R53,100k,SpaghettiLAB:R0603,C25803,no
R54,100k,SpaghettiLAB:R0603,C25803,no
R55,100k,SpaghettiLAB:R0603,C25803,no
R56,0R,Resistor_SMD:R_1206_3216Metric,C17888,no
R57,0R,Resistor_SMD:R_1206_3216Metric,C17888,no
R58,0R,Resistor_SMD:R_1206_3216Metric,C17888,no
R59,0R,Resistor_SMD:R_1206_3216Metric,C17888,no
R60,0R,Resistor_SMD:R_1206_3216Metric,C17888,no
R61,0R,Resistor_SMD:R_1206_3216Metric,C17888,no
R78,100k,Resistor_SMD:R_0603_1608Metric,C25803,no
TP8,SMD/0.6mm,TestPoint:TestPoint_Pad_D1.0mm,,no
TP9,SMD/0.6mm,TestPoint:TestPoint_Pad_D1.0mm,,no
TP12,SMD/0.6mm,TestPoint:TestPoint_Pad_D1.0mm,,no
TP13,SMD/0.6mm,TestPoint:TestPoint_Pad_D1.0mm,,no
TP15,SMD/0.6mm,TestPoint:TestPoint_Pad_D1.0mm,,no
TP18,SMD/0.6mm,TestPoint:TestPoint_Pad_D1.0mm,,no
TP19,SMD/0.6mm,TestPoint:TestPoint_Pad_D1.0mm,,no
TP21,SMD/0.6mm,TestPoint:TestPoint_Pad_D1.0mm,,no
TP22,AG_NRST,TestPoint:TestPoint_Pad_D1.0mm,,no
TP23,AG_JTMS,TestPoint:TestPoint_Pad_D1.0mm,,no
TP24,AG_JTCK,TestPoint:TestPoint_Pad_D1.0mm,,no
TP25,AG_JTDI,TestPoint:TestPoint_Pad_D1.0mm,,no
TP26,AG_JTDO,TestPoint:TestPoint_Pad_D1.0mm,,no
TP27,AG_JNTRST,TestPoint:TestPoint_Pad_D1.0mm,,no
TP41,DAC1_SPARE,TestPoint:TestPoint_Pad_D1.0mm,,no
TP42,SPARE_IO_17,TestPoint:TestPoint_Pad_D1.0mm,,no
TP43,SPARE_IO_33,TestPoint:TestPoint_Pad_D1.0mm,,no
TP44,SPARE_IO_34,TestPoint:TestPoint_Pad_D1.0mm,,no
TP45,ISO4_CTRL,TestPoint:TestPoint_Pad_D1.0mm,,no
TP46,ISO5_CTRL,TestPoint:TestPoint_Pad_D1.0mm,,no
TP47,AG_UART_RX,TestPoint:TestPoint_Pad_D1.0mm,,no
TP48,AG_UART_TX,TestPoint:TestPoint_Pad_D1.0mm,,no
TP49,AG_BOOT0,TestPoint:TestPoint_Pad_D1.0mm,,no
U1,ESP32-S3-WROOM-1_1U_FlexyPin_Socket,FlexyPin:ESP32-S3-WROOM-1_1U_FlexyPin_Socket,C2913201,no
U2,SN65HVD230DR,SpaghettiLAB:SOIC-8_L4.9-W3.9-P1.27-LS6.0-BL,C12084,no
U3,HC-TYPE-C-16P-01A,SpaghettiLAB:USB-C-SMD_HC-TYPE-C-16P-01A,C2894897,no
U4,TPS562201DDCR,SpaghettiLAB:TSOT-23-6_Power,C90061,no
U8,G3VM-61VY3,SpaghettiLAB:SMD-4_L4.6-W3.7-P2.54-LS7.0-TL,C2152318,no
U12,SN74CBTLV3125PWR,LCSC_Ports:TSSOP-14_L5.0-W4.4-P0.65-LS6.4-BL,C406866,no
U13,SN74CBTLV3125PWR,LCSC_Ports:TSSOP-14_L5.0-W4.4-P0.65-LS6.4-BL,C406866,no
U25,TCA9535PWR(UMW),LCSC_Ports:TSSOP-24_L7.8-W4.4-P0.65-LS6.4-BL,C22396388,no
C124,100nF,Capacitor_SMD:C_0603_1608Metric,C14663,no
U26,SN74LVC1G3157DCKR,Package_TO_SOT_SMD:SOT-363_SC-70-6,C38663,no
U27,SN74LVC1G3157DCKR,Package_TO_SOT_SMD:SOT-363_SC-70-6,C38663,no
U28,SN74LVC1G3157DCKR,Package_TO_SOT_SMD:SOT-363_SC-70-6,C38663,no
U29,SN74LVC1G3157DCKR,Package_TO_SOT_SMD:SOT-363_SC-70-6,C38663,no
U30,SN74LVC1G3157DCKR,Package_TO_SOT_SMD:SOT-363_SC-70-6,C38663,no
C125,100nF,Capacitor_SMD:C_0402_1005Metric,C1525,no
C126,100nF,Capacitor_SMD:C_0402_1005Metric,C1525,no
C127,100nF,Capacitor_SMD:C_0402_1005Metric,C1525,no
C128,100nF,Capacitor_SMD:C_0402_1005Metric,C1525,no
C129,100nF,Capacitor_SMD:C_0402_1005Metric,C1525,no
R103,100k,Resistor_SMD:R_0402_1005Metric,C25741,no
R104,47k,Resistor_SMD:R_0402_1005Metric,C25792,no
R105,100k,Resistor_SMD:R_0402_1005Metric,C25741,no
R106,100k,Resistor_SMD:R_0402_1005Metric,C25741,no
R108,100k,Resistor_SMD:R_0402_1005Metric,C25741,no
